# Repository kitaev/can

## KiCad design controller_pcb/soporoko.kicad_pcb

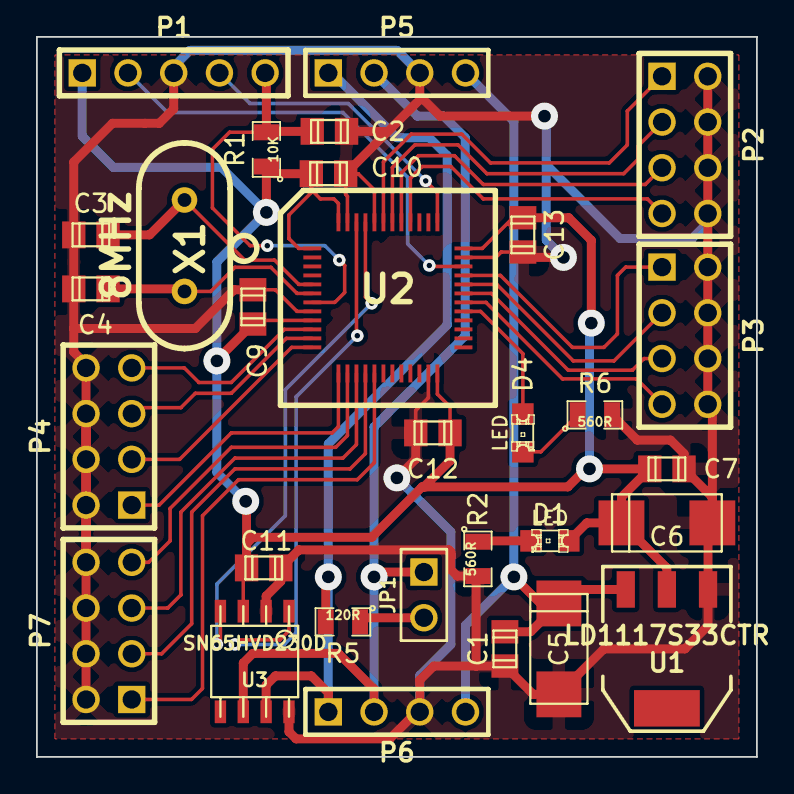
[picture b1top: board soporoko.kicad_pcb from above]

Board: 2 copper layers, 40.0 x 40.0 mm, 30 parts (0 on the bottom side), 32 nets.

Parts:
C1, C7, C9, C10, C11, C12, C13: 100nF; c_0805
C2: 180pF; c_0805
C3, C4: 20pF; c_0805
C5, C6: 10uF; c_tant_C
D1, D4: LED; LED-0805
JP1: JUMPER; PIN_ARRAY_2X1
P1: SWD; PIN_ARRAY_5x1
P2, P3, P4, P7: CONN_4X2; pin_array_4x2
P5, P6: CONN_4; PIN_ARRAY_4x1
R1: 10K; SM0805
R2, R6: 560R; SM0805
R5: 120R; SM0805
U1: LD1117S33CTR; SOT223
U2: STM32F303; lqfp48
U3: SN65HVD230D; so-8
X1: 8MHz; HC-49V

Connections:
+12V: C1.1, C5.1, P5.4, P6.4, U1.3
/C0: P2.1, U2.43
/C1: P2.3, U2.42
/C2: P2.5, U2.41
/C3: P2.7, U2.40
/C4: P3.1, U2.33
/C5: P3.3, U2.32
/C6: P3.5, U2.31
/C7: P3.7, U2.30
/C8: P7.1, U2.17
/C9: P7.3, U2.16
/C10: P7.5, U2.15
/C11: P7.7, U2.14
/C12: P4.1, U2.13
/C13: P4.3, U2.12
/C14: P4.5, U2.11
/C15: P4.7, U2.10
/CANH: P5.1, P6.1, R5.2, U3.7
/CANL: JP1.1, P5.2, P6.2, U3.6
/CAN_RX: U2.45, U3.4
/CAN_TX: U2.46, U3.1
/LED: D4.1, U2.29
/NRST: C2.1, P1.5, R1.2, U2.7
/OSCIN: C3.1, U2.5, X1.1
/OSCOUT: C4.1, U2.6, X1.2
/SWCLK: P1.4, U2.37
/SWDIO: P1.2, U2.34
/Vdd: C6.1, C7.1, C9.1, C10.1, C11.1, C12.1, C13.1, D1.1, P1.1, R1.1, U1.2, U2.1, U2.9, U2.24, U2.36, U2.48, U3.3
GND: C1.2, C2.2, C3.2, C4.2, C5.2, C6.2, C7.2, C9.2, C10.2, C11.2, C12.2, C13.2, P1.3, P2.2, P2.4, P2.6, P2.8, P3.2, P3.4, P3.6, P3.8, P4.2, P4.4, P4.6, P4.8, P5.3, P6.3, P7.2, P7.4, P7.6, P7.8, R2.2, R6.2, U1.1, U2.8, U2.23, U2.35, U2.44, U2.47, U3.2, U3.8
unnamed: D4.2, R6.1
unnamed: D1.2, R2.1
unnamed: JP1.2, R5.1

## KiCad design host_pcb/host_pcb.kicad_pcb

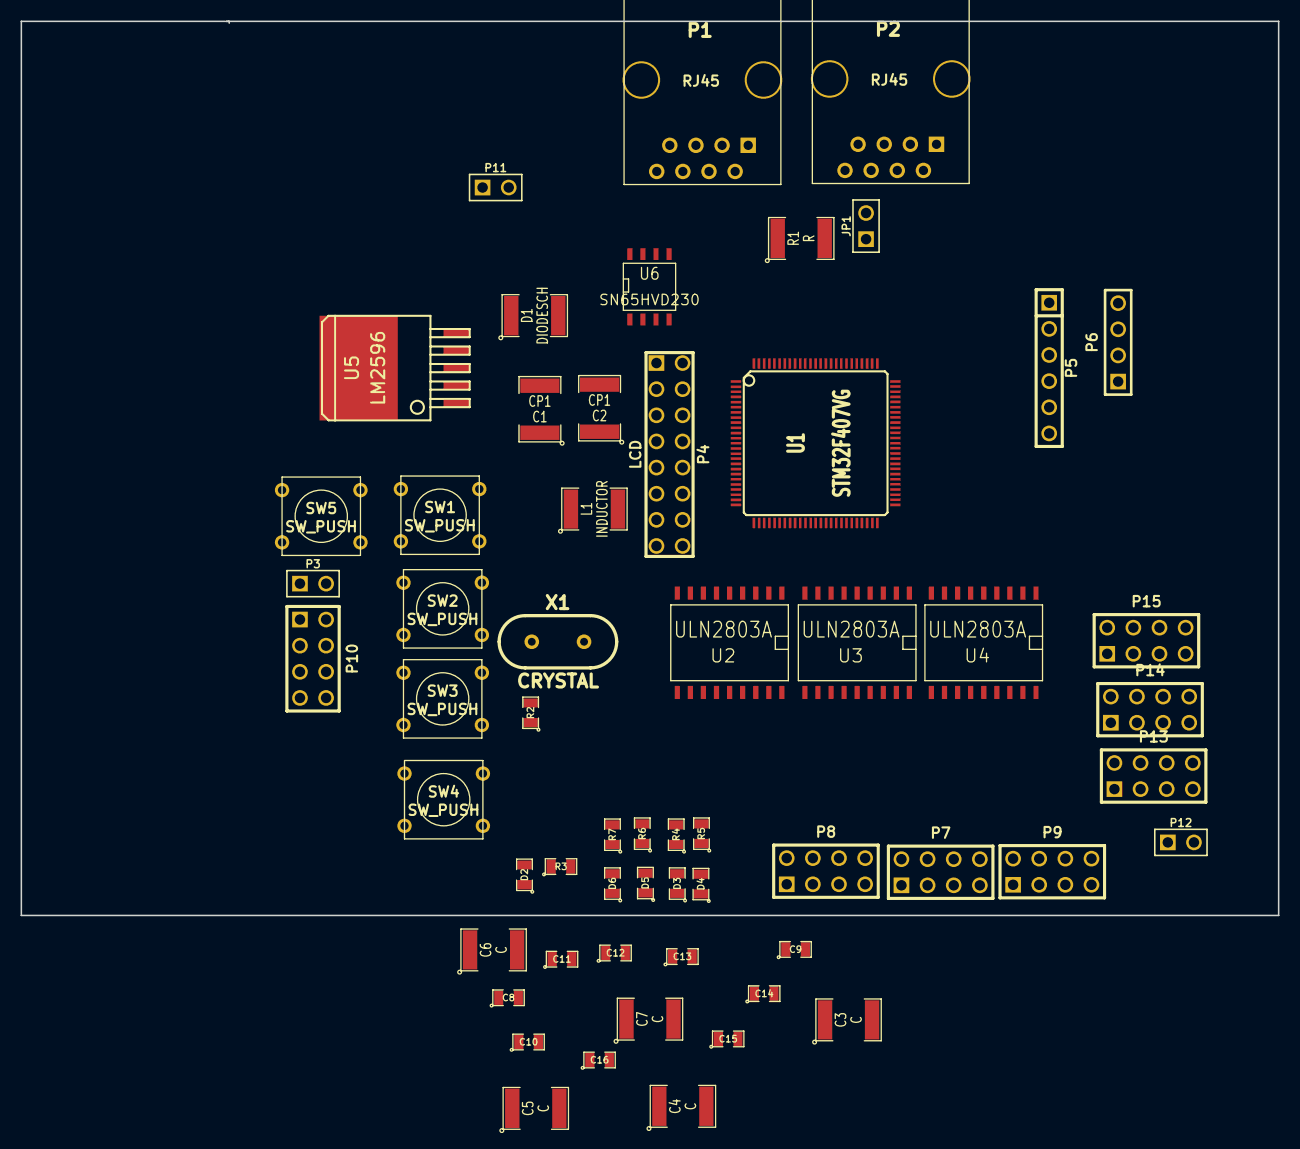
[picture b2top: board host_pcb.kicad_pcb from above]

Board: 2 copper layers, 122.2 x 86.9 mm, 58 parts (0 on the bottom side), 115 nets, no tracks yet.

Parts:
C1, C2: CP1; SM1812
C3, C4, C5, C6, C7: C; SM1812
C8, C9, C10, C11, C12, C13, C14, C15, C16: CSMALL; SM0805
D1: DIODESCH; SM1812
D2, D3, D4, D5, D6: LED; SM0805
JP1: JUMPER; PIN_ARRAY_2X1
L1: INDUCTOR; SM1812
P1, P2: RJ45; RJ45_8
P3: RST; PIN_ARRAY_2X1
P4: LCD; pin_array_8x2
P5: SWD; PIN_ARRAY-6X1
P6: UART2; PIN_ARRAY_4x1
P7: IN_1; pin_array_4x2
P8: IN_2; pin_array_4x2
P9: IN_3; pin_array_4x2
P10: BTNS; pin_array_4x2
P11: PWR_IN; PIN_ARRAY_2X1
P12: PWR_OUT; PIN_ARRAY_2X1
P13: OUT_1; pin_array_4x2
P14: OUT_2; pin_array_4x2
P15: OUT_3; pin_array_4x2
R1: R; SM1812
R2, R3, R4, R5, R6, R7: R; SM0805
SW1, SW2, SW3, SW4, SW5: SW_PUSH; SW_PUSH_SMALL
U1: STM32F407VG; VQFP100
U2, U3, U4: ULN2803A; SO18L
U5: LM2596; TO263-5
U6: SN65HVD230; SO8N
X1: CRYSTAL; HC-49V

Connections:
3v3: C2.1, C8.1, C9.1, C10.1, C11.1, C12.1, D2.1, L1.2, P4.2, P5.1, P6.4, U1.6, U1.11, U1.19, U1.21, U1.22, U1.28, U1.50, U1.75, U1.100, U5.4, U6.3
12v: C1.1, P1.1, P1.2, P2.1, P2.2, P11.1, P12.1, U2.10, U3.10, U4.10, U5.1
/a1: P7.1, U1.56
/a2: P7.2, U1.57
/a3: P7.3, U1.58
/a4: P7.4, U1.59
/a5: P7.5, U1.60
/a6: P7.6, U1.61
/a7: P7.7, U1.62
/a8: P7.8, U1.63
/a9: P8.1, U1.64
/a10: P8.2, U1.65
/a11: P8.3, U1.66
/a12: P8.4, U1.67
/a13: P8.5, U1.68
/a14: P8.6, U1.69
/a15: P8.7, U1.70
/a16: P8.8, U1.71
/a17: P9.1, U1.77
/a18: P9.2, U1.78
/a19: P9.3, U1.79
/a20: P9.4, U1.80
/a21: P9.5, U1.81
/a22: P9.6, U1.82
/a23: P9.7, U1.83
/a24: P9.8, U1.84
/b1: U1.29, U2.8
/b2: U1.30, U2.7
/b3: U1.31, U2.6
/b4: U1.32, U2.5
/b5: U1.33, U2.4
/b6: U1.34, U2.3
/b7: U1.35, U2.2
/b8: U1.36, U2.1
/b9: U1.37, U3.8
/b10: U1.38, U3.7
/b11: U1.39, U3.6
/b12: U1.40, U3.5
/b13: U1.41, U3.4
/b14: U1.42, U3.3
/b15: U1.43, U3.2
/b16: U1.44, U3.1
/b17: U1.45, U4.8
/b18: U1.46, U4.7
/b19: U1.47, U4.6
/b20: U1.48, U4.5
/b21: U1.51, U4.4
/b22: U1.52, U4.3
/b23: U1.53, U4.2
/b24: U1.54, U4.1
/d1: P13.1, U2.11
/d2: P13.2, U2.12
/d3: P13.3, U2.13
/d4: P13.4, U2.14
/d5: P13.5, U2.15
/d6: P13.6, U2.16
/d7: P13.7, U2.17
/d8: P13.8, U2.18
/d9: P14.1, U3.11
/d10: P14.2, U3.12
/d11: P14.3, U3.13
/d12: P14.4, U3.14
/d13: P14.5, U3.15
/d14: P14.6, U3.16
/d15: P14.7, U3.17
/d16: P14.8, U3.18
/d17: P15.1, U4.11
/d18: P15.2, U4.12
/d19: P15.3, U4.13
/d20: P15.4, U4.14
/d21: P15.5, U4.15
/d22: P15.6, U4.16
/d23: P15.7, U4.17
/d24: P15.8, U4.18
/ld0: P4.7, U1.7
/ld1: P4.8, U1.8
/ld2: P4.9, U1.1
/ld3: P4.10, U1.2
/ld4: P4.11, U1.3
/ld5: P4.12, U1.4
/ld6: P4.13, U1.5
/ld7: P4.14, U1.15
/le: P4.6, U1.18
/lrs: P4.4, U1.16
/lrw: P4.5, U1.17
Net-<C4-Pad2>: C4.2, R2.1, X1.1
Net-<C6-Pad1>: C6.1, U1.49
Net-<C7-Pad1>: C7.1, U1.73
Net-<C13-Pad1>: C13.1, C14.1, C15.1, C16.1
Net-<D1-Pad2>: D1.2, L1.1, U5.2
Net-<D2-Pad2>: D2.2, R3.1
Net-<D3-Pad2>: D3.2, R4.1
Net-<D4-Pad2>: D4.2, R5.1
Net-<D5-Pad2>: D5.2, R6.1
Net-<D6-Pad2>: D6.2, R7.1
Net-<JP1-Pad1>: JP1.1, R1.2
btn0: P10.1, SW2.1, U1.90
btn1: P10.3, SW3.1, U1.91
btn2: P10.5, SW4.1, U1.92
btn3: P10.7, SW5.1, U1.93
can1_rx: U1.95, U6.4
can1_tx: U1.96, U6.1
canh: JP1.2, P1.7, P2.7, U6.7
canl: P1.8, P2.8, R1.1, U6.6
led0: D3.1, U1.85
led1: D4.1, U1.86
led2: D5.1, U1.87
led3: D6.1, U1.88
nrst: C5.1, P3.2, P5.5, SW1.2, U1.14
oscin: C3.2, U1.12, X1.2
oscout: R2.2, U1.13
swclk: P5.2, U1.76
swdio: P5.4, U1.72
traceswo: P5.6, U1.89
vss: C1.2, C2.2, C3.1, C4.1, C5.2, C6.2, C7.2, C8.2, C9.2, C10.2, C11.2, C12.2, C13.2, C14.2, C15.2, C16.2, D1.1, P1.4, P1.5, P2.4, P2.5, P3.1, P4.1, P5.3, P6.1, P10.2, P10.4, P10.6, P10.8, P11.2, P12.2, R3.2, R4.2, R5.2, R6.2, R7.2, SW1.1, SW2.2, SW3.2, SW4.2, SW5.2, U1.10, U1.20, U1.27, U1.74, U1.94, U1.99, U2.9, U3.9, U4.9, U5.3, U5.5, U6.2, U6.8

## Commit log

2013-04-11 host project added (stm32f30x), projects set up is in progress.
2013-04-11 main.c sample code removed
2013-04-11 Host: make shows binary size; all gcc size optimizations are turned on.
2013-04-12 Eclipse project: default make is used instead of hardcoded.
2013-04-12 Host makefile: flash command added.
2013-04-12 Host: simple sleepy blinker implemented with SPL.
2013-04-12 Host: unused code removed.
2013-04-12 Host: Eclipse debug and openocd launch configurations added, unused variables removed from project settings, makefile all target no longer calls clean.
2013-04-12 Host: timer prescaler and period changed to make period fit into 0x0000:0xFFFF bounds.
2013-04-25 Project for STM8S208 controller added.
2013-04-25 SPL CAN library added, along with required cosmic machine library and startup code with data initialization; Simple CAN loopback tested.
2013-04-26 Simple debounce code.
2013-04-27 semi-automated interrupt handlers definition support - no need to change stm8_interrupt_vector.c to add new interrupt.
2013-05-08 Project for host based on stm32f4 added. Button on GPIOA_0 toggles LEDs.
2013-05-09 controller: CAN configuration adjusted to match that of the host (125Kb/s, 13/2/1).
2013-05-09 host: Simple CAN tranceiver implementation, baud rate 125Kb/s, 13/2/1 bit segments.
2013-05-10 host: clock configuration (external 24Mhz crystal used) added.
2013-05-11 host: UART-based debug print facility added.
2013-10-20 Control 100ms impulse now sent on PC2 when CAN message received.
2013-10-21 WIP: host pcb project
2013-10-21 WIP: host PCB
2013-10-28 altium project
2013-10-29 controller project for stm32f303
2013-10-30 controller board project
2013-10-31 local makefile template
2013-12-04 Altium project update
